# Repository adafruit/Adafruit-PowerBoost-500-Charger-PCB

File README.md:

# Adafruit PowerBoost 500 Charger PCB
<a href="http://www.adafruit.com/products/1944"><br/>
Click here to purchase one from the Adafruit shop
</a>

The PowerBoost 500C is the perfect power supply for your portable project! With a built-in battery charger circuit, you'll be able to keep your project running even while recharging the battery! This little DC/DC boost converter module can be powered by any 3.7V LiIon/LiPoly battery, and convert the battery output to 5.2V DC for running your 5V projects.

Like our popular 5V 1A USB wall adapter, the output has been tweaked to be 5.2V instead of a straight-up 5.0V so that there's a little bit of 'headroom' for long cables, high draw, the addition of a diode on the output if you wish, etc. The 5.2V is safe for all 5V-powered electronics like Arduino, Adafruit Metro, Raspberry Pi, or BeagleBone while preventing icky brown-outs during high current draw because of USB cable resistance.

The PowerBoost 500C has at the heart a TPS61090 boost converter from TI. This boost converter chip has some really nice extras such as low battery detection, 2A internal switch, synchronous conversion, excellent efficiency, and 700KHz high-frequency operation.

This repo contains the PCB files for the Adafruit PowerBoost 500 Charger

### License

Adafruit invests time and resources providing this open source design, please support Adafruit and open-source hardware by purchasing products from [Adafruit](https://www.adafruit.com)!

All text above must be included in any redistribution

Designed by Limor Fried/Ladyada for Adafruit Industries.
Creative Commons Attribution/Share-Alike, all text above must be included in any redistribution. 
See license.txt for additional information.

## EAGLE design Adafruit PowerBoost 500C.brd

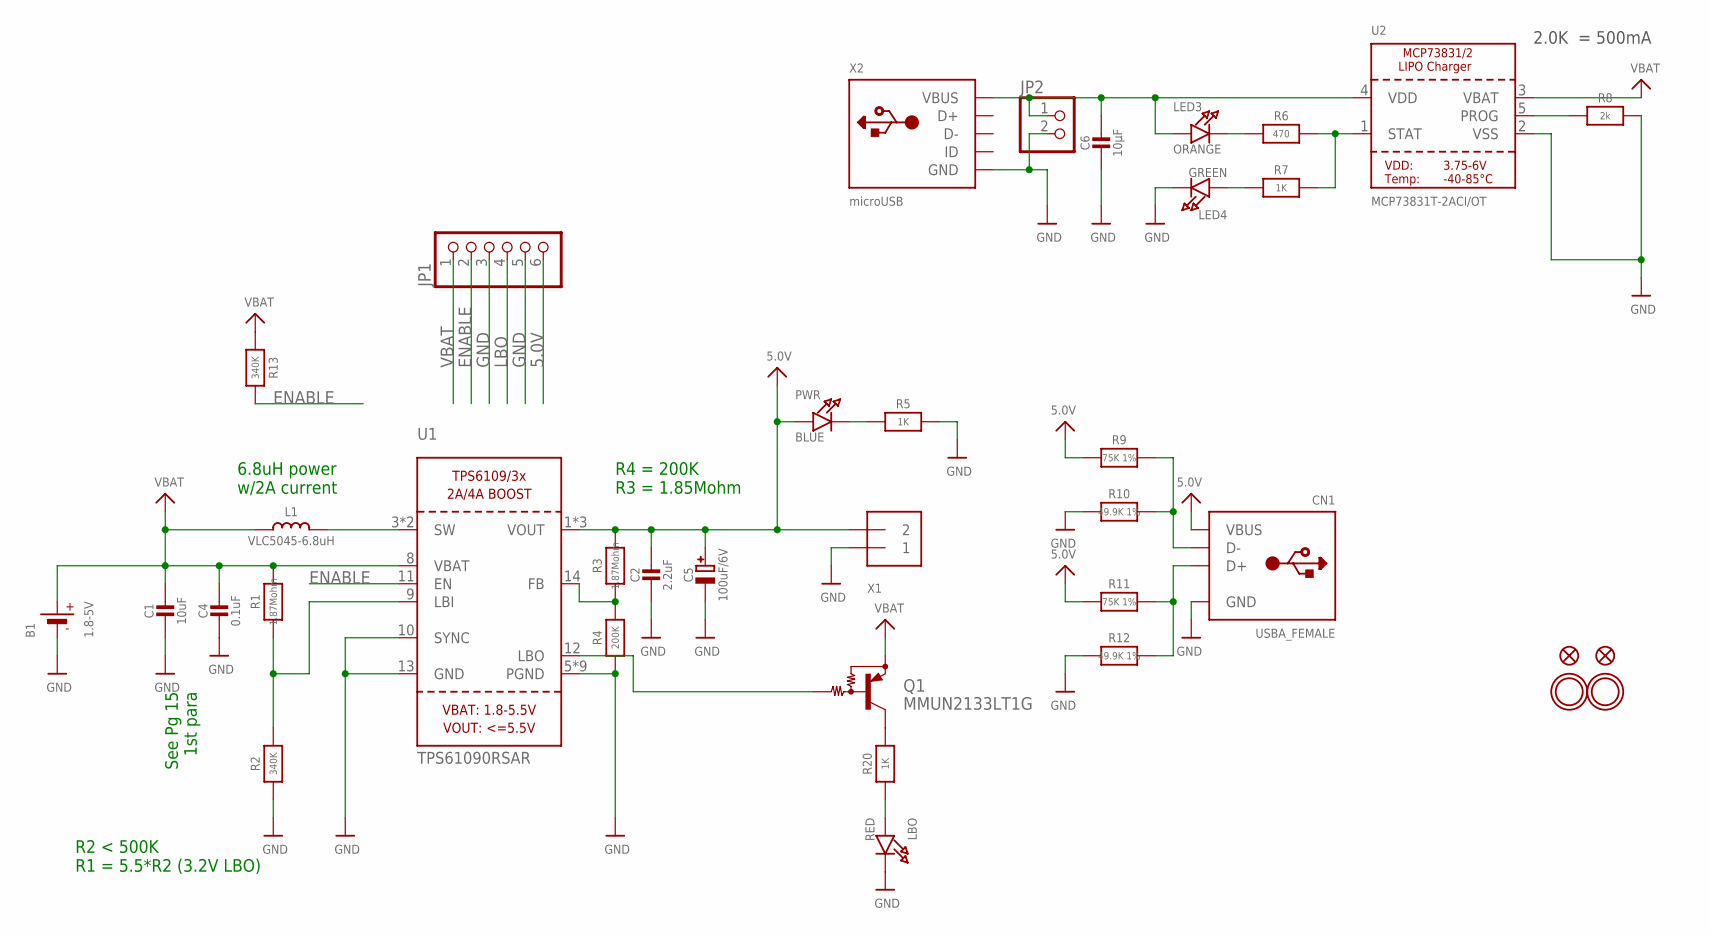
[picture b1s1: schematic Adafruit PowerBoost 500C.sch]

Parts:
B1: 1.8-5V; JSTPH2
C1: 10uF; 0805-NO
C2: 2.2uF; 0805-NO
C4: 0.1uF; 0805-NO
C5: 100uF/6V; EIA3528-21/B-R
C6: 10µF; 0805-NO
CN1: USBA_FEMALE; USB_HOST-PTH
FID2, FID3: FIDUCIAL""; FIDUCIAL_1MM
JP1: PINHD-1X6CB; 1X06-CLEANBIG
JP2: HEADER-1X2ROUND; 1X02_ROUND
L1: VLC5045-6.8uH; INDUCTOR_5X5MM_TDK_VLC5045
LBO: RED; CHIPLED_0805_NOOUTLINE
LED3: ORANGE; CHIPLED_0805_NOOUTLINE
LED4: GREEN; CHIPLED_0805_NOOUTLINE
PWR: BLUE; CHIPLED_0805_NOOUTLINE
Q1: MMUN2133LT1G; SC59-BEC
R1, R3: 1.87Mohm; 0805-NO
R2, R13: 340K; 0805-NO
R4: 200K; 0805-NO
R5, R7, R20: 1K; 0805-NO
R6: 470; 0805-NO
R8: 2k; 0805-NO
R9, R11: 75K 1%; 0805-NO
R10, R12: 49.9K 1%; 0805-NO
U1: TPS61090RSAR; PVQFN-16
U2: MCP73831T-2ACI/OT; SOT23-5
U$10, U$12: MOUNTINGHOLE2.5; MOUNTINGHOLE_2.5_PLATED
X1: TERMBLOCK_1X2; TERMBLOCK_1X2-3.5MM
X2: microUSB; 4UCONN_20329

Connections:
5.0V: C2.1, C5.+, CN1.VBUS, JP1.6, PWR.A, R3.2, R9.2, R11.2, U1.1 (VOUT), U1.15 (VOUT), U1.16 (VOUT), X1.2
D+: CN1.D+, R11.1, R12.1
D-: CN1.D-, R9.1, R10.1
ENABLE: JP1.2, R13.2, U1.11 (EN)
GND: B1.1 (-), C1.2, C2.2, C4.2, C5.-, C6.2, CN1.GND, JP1.3, JP1.5, JP2.2, LBO.C, LED4.C, R2.1, R4.1, R5.2, R8.2, R10.2, R12.2, U1.5 (PGND), U1.6 (PGND), U1.7 (PGND), U1.10 (SYNC), U1.13 (GND), U1.P$18 (PGND), U1.P$19 (PGND), U1.P$20 (PGND), U1.P$21 (PGND), U1.P$22 (PGND), U1.THERMAL (PGND), U2.2 (VSS), X1.1, X2.BASE@1 (GND), X2.BASE@2 (GND), X2.GND, X2.SPRT@1 (GND), X2.SPRT@2 (GND), X2.SPRT@3 (GND), X2.SPRT@4 (GND)
LBO: JP1.4, Q1.B, U1.12 (LBO)
unnamed: L1.P$2 (2), U1.3 (SW), U1.4 (SW)
unnamed: LBO.A, R20.1
unnamed: R1.1, R2.2, U1.9 (LBI)
unnamed: PWR.C, R5.1
unnamed: R3.1, R4.2, U1.14 (FB)
unnamed: LED3.C, R6.1
unnamed: R6.2, R7.2, U2.1 (STAT)
unnamed: R8.1, U2.5 (PROG)
unnamed: LED4.A, R7.1
unnamed: Q1.C, R20.2
VBAT: B1.2 (+), C1.1, C4.1, JP1.1, L1.P$1 (1), Q1.E, R1.2, R13.1, U1.8 (VBAT), U2.3 (VBAT)
VDD1: C6.1, JP2.1, LED3.A, U2.4 (VDD), X2.VBUS

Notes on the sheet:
See Pg 15 1st para
6.8uH power w/2A current
R2 < 500K R1 = 5.5*R2 (3.2V LBO)
R4 = 200K R3 = 1.85Mohm
2.0K = 500mA

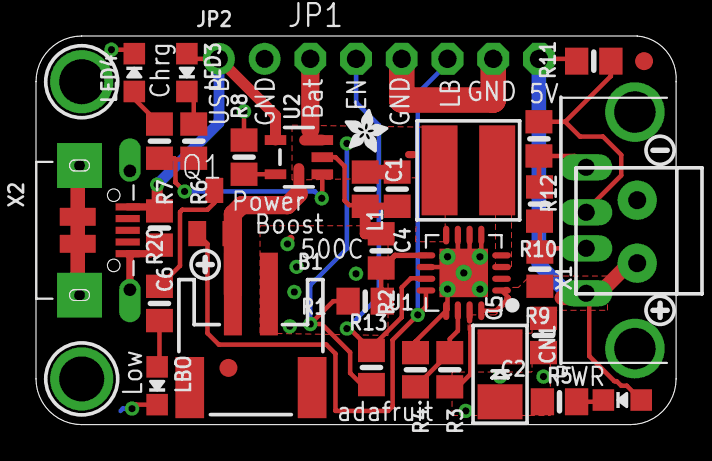
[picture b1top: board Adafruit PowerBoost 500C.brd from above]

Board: 2 copper layers, 35.6 x 21.6 mm, 42 parts (1 on the bottom side), 18 nets.

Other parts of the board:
U$13, U$25: SYMBOL_PLUS
U$26: SYMBOL_MINUS
U$28: ADAFRUIT_2.5MM
U$29: ADAFRUIT_5MM

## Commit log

2015-01-14 init

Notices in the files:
parts and their libraries:
microbuilder: This work is placed in the public domain, and may be freely used for commercial and non-commercial work with the following conditions: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
